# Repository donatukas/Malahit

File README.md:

* Malachite SDR

     * 50KHz-250MHz+400-2000MHz DSP SDR Receiver
     * DSP SDR Receiver for Malahit
     * Capacitive touch screen
     * Flash via USB cable
     * Default frequency range: 50KHz-2000MHz
     * 3.5 inch capacitive screen

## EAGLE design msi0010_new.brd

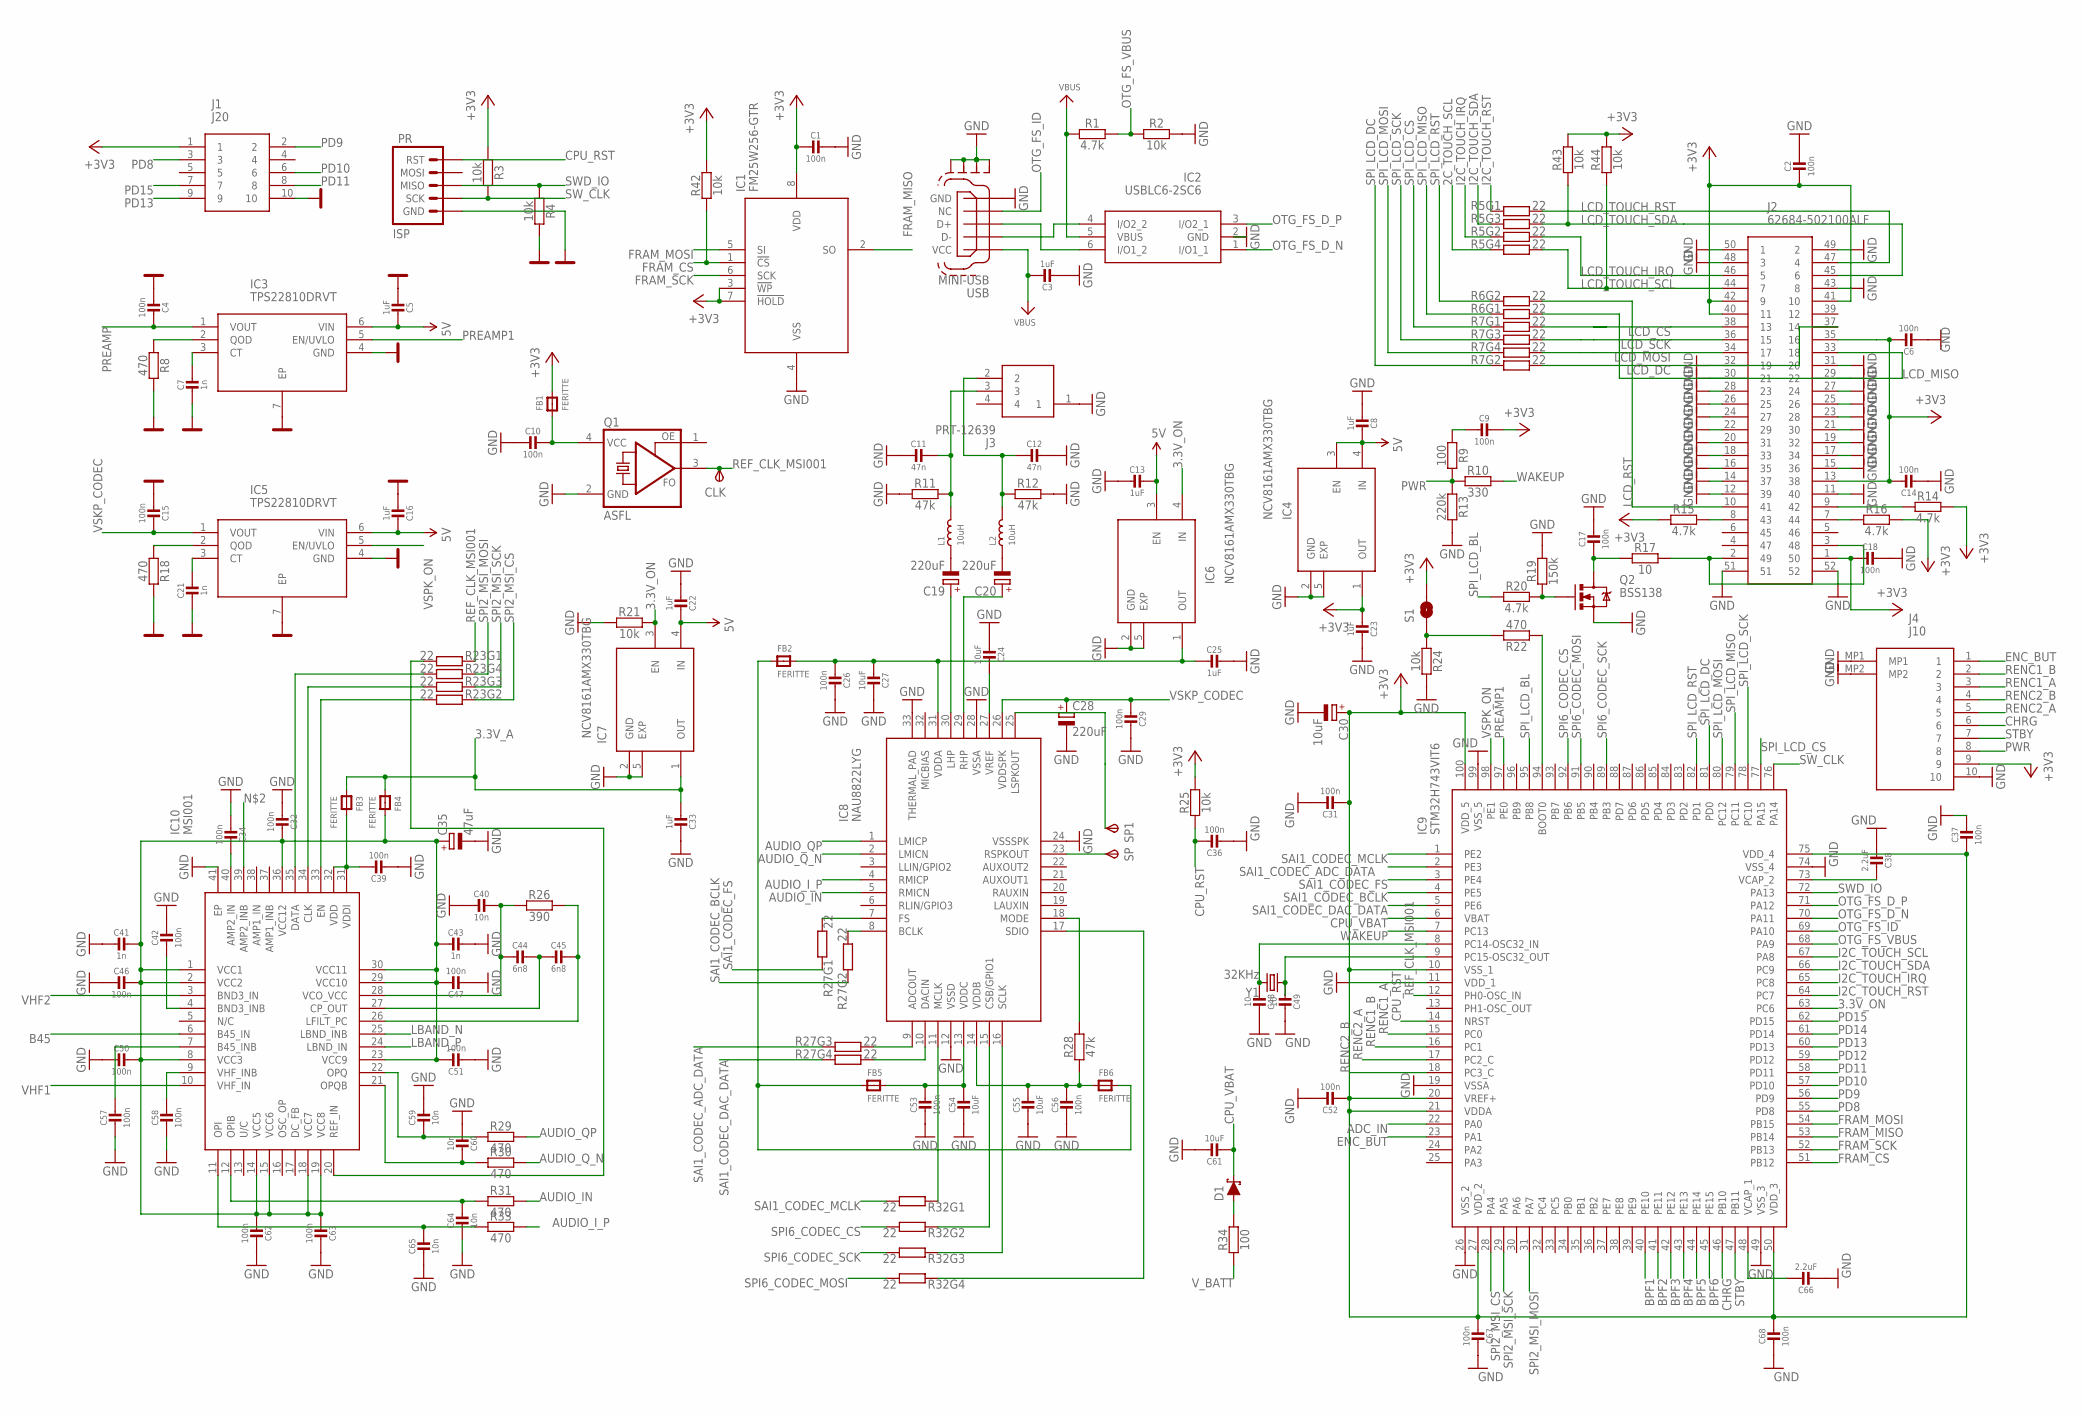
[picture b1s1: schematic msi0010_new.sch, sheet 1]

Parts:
C1, C2, C4, C6, C9, C10, C14, C15, C17, C18, C29, C31, C32, C34, C36, C37, C39, C42, C46, C47, C50, C51, C52, C53, C57, C58, C62, C63, C67, C68: 100n; _0402
C3, C5, C8, C13, C16, C22, C23, C25, C33: 1uF; _0603
C7, C21, C41, C43: 1n; _0402
C11, C12: 47n; _0402
C19, C20, C28: 220uF; SANYO-OSCON_A
C24, C27, C55, C61: 10uF; _0402
C26, C56: 100n; _0603
C30: 10uF; SMC_A
C35: 47uF; SMC_A
C38, C66: 2.2uF; 0805_NOTHERMALS
C40, C59, C60, C64, C65: 10n; _0402
C44, C45: 6n8; _0402
C48, C49: 10; _0402
C54: 10uF; _0603
CLK: TPSTP13R; TP13R
D1: 1A/40V/500mV; SOD-323
FB1, FB2, FB3, FB4, FB5, FB6: FERITTE; _0603
IC1: FM25W256-GTR; SOT127P602X173-8N
IC2: USBLC6-2SC6; SOT95P280X145-6N
IC3, IC5: TPS22810DRVT; SON65P200X200X80-7N
IC4, IC6, IC7: NCV8161AMX330TBG; VREG_NCP170AMX285TCG
IC8: NAU8822LYG; QFN50P500X500X80-33N
IC9: STM32H743VIT6; QFP50P1600X1600X160-100N
IC10: MSI001; QFN50P600X600X90-41N
J1: J20; 3220-10-0300-00-TR_322010030000TR
J2: 62684-502100ALF; 62684502100ALF
J3: PRT-12639; PRT12639
J4: J10; 686120148922_686120148922
L1, L2: 10uH; L0805@1
PR: ISP; SPARKFUN-CONNECTORS_PIC-ICSP-MINI
Q1: ASFL; ASF
Q2: BSS138; SOT23-3
R1, R14, R15, R16, R20: 4.7k; C0402
R2, R3, R4, R21, R24, R25, R42, R43, R44: 10k; C0402
R5, R6, R7, R23, R27, R32: 22; R_MATRIX_4_0402
R8, R18, R22, R29, R30, R31, R33: 470; C0402
R9, R34: 100; C0402
R10: 330; C0402
R11, R12, R28: 47k; C0402
R13: 220k; C0402
R17: 10; C0805
R19: 150k; C0402
R26: 390; C0402
S1: SOLDERJUMPERNO; SJ_2S-NO
SP, SP1: TPSTP15R; TP15R
USB: MINI-USB; MINI-USB-B5
Y1: 32KHz; CRYSTAL-32KHZ-MS3V

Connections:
2C_TOUCH_SCL: R5.4.1 (1)
3.3V_A: C33.2, FB3.1, FB4.1, IC7.1 (OUT); also elsewhere on the board
3.3V_ON: IC6.4 (IN), IC7.3 (EN), IC9.63 (PC6), R21.2
5V: C5.1, C8.1, C13.1, C16.1, C22.1, IC3.6 (VIN), IC4.3 (EN), IC4.4 (IN), IC5.6 (VIN), IC6.3 (EN), IC7.4 (IN); also elsewhere on the board
+3V3: C1.2, C2.2, C6.1, C9.1, C14.1, C18.2, C23.2, C30.+, C31.2, C37.2, C52.2, C67.2, C68.1, FB1.2, IC1.3 (!WP), IC1.7 (!HOLD), IC1.8 (VDD), IC4.1 (OUT), IC9.10 (VSS_1), IC9.20 (VREF+), IC9.21 (VDDA), IC9.27 (VDD_2), IC9.50 (VDD_3), IC9.75 (VDD_4), IC9.100 (VDD_5), J1.1, J2.1 (50), J2.13 (38), J2.35 (16), J2.40 (11), J2.41 (10), J2.42 (9), J4.9, R3.1, R14.2, R15.1, R16.2, R25.2, R42.2, R43.2, R44.2, S1.2; also elsewhere on the board
-: IC8.25 (LSPKOUT), SP1.TP
ADC_IN: IC9.22 (PA0); also elsewhere on the board
AUDIO_IN: IC8.5 (RMICN), R31.2
AUDIO_I_P: IC8.4 (RMICP), R33.2
AUDIO_QP: IC8.1 (LMICP), R29.2
AUDIO_Q_N: IC8.2 (LMICN), R30.2
B45: IC10.6 (B45_IN); also elsewhere on the board
BPF1: IC9.40 (PE10); also elsewhere on the board
BPF2: IC9.41 (PE11); also elsewhere on the board
BPF3: IC9.42 (PE12); also elsewhere on the board
BPF4: IC9.43 (PE13); also elsewhere on the board
BPF5: IC9.44 (PE14); also elsewhere on the board
BPF6: IC9.45 (PE15); also elsewhere on the board
CHRG: IC9.46 (PB10), J4.6; also elsewhere on the board
CPU_RST: C36.1, IC9.14 (NRST), PR.1 (RST), R25.1
CPU_VBAT: C61.2, D1.C, IC9.6 (VBAT)
ENC_BUT: IC9.23 (PA1), J4.1
FRAM_CS: IC1.1 (!CS), IC9.51 (PB12), R42.1
FRAM_MISO: IC1.2 (SO), IC9.53 (PB14)
FRAM_MOSI: IC1.5 (SI), IC9.54 (PB15)
FRAM_SCK: IC1.6 (SCK), IC9.52 (PB13)
GND: C1.1, C2.1, C3.2, C4.2, C5.2, C6.2, C7.2, C8.2, C10.2, C11.2, C12.1, C13.2, C14.2, C15.2, C16.2, C17.1, C18.1, C21.2, C22.2, C23.1, C24.2, C25.1, C26.1, C27.1, C28.-, C29.1, C30.-, C31.1, C32.2, C33.1, C34.2, C35.-, C36.2, C37.1, C38.2, C39.2, C40.2, C41.2, C42.1, C43.1, C46.2, C47.2, C48.1, C49.1, C50.2, C51.2, C52.1, C53.2, C54.2, C55.2, C56.2, C57.2, C58.2, C59.1, C60.2, C61.1, C62.1, C63.1, C64.2, C65.2, C66.2, C67.1, C68.2, IC1.4 (VSS), IC2.2 (GND), IC3.4 (GND), IC3.7 (EP), IC4.2 (GND), IC4.5 (EXP), IC5.4 (GND), IC5.7 (EP), IC6.2 (GND), IC6.5 (EXP), IC7.2 (GND), IC7.5 (EXP), IC8.12 (VSSD), IC8.24 (VSSSPK), IC8.28 (VSSA), IC8.33 (THERMAL_PAD), IC9.11 (VDD_1), IC9.19 (VSSA), IC9.26 (VSS_2), IC9.49 (VSS_3), IC9.74 (VSS_4), IC9.99 (VSS_5), IC10.41 (EP), J1.10, J2.11 (40), J2.12 (39), J2.14 (37), J2.15 (36), J2.16 (35), J2.17 (34), J2.18 (33), J2.19 (32), J2.20 (31), J2.21 (30), J2.22 (29), J2.23 (28), J2.24 (27), J2.25 (26), J2.26 (25), J2.27 (24), J2.28 (23), J2.29 (22), J2.30 (21), J2.31 (20), J2.32 (19), J2.43 (8), J2.48 (3), J2.49 (2), J2.50 (1), J2.51, J2.52, J3.1, J4.10, J4.MP1, J4.MP2, PR.5 (GND), Q1.2 (GND), Q2.2 (S), R2.2, R4.2, R8.2, R11.1, R12.2, R13.2, R18.2, R19.2, R21.1, R24.2, USB.5 (GND), USB.M1 (S1), USB.M2 (S2), USB.M3 (S3), USB.M4 (S4); also elsewhere on the board
I2C_TOUCH_IRQ: IC9.65 (PC8), R5.2.1 (1)
I2C_TOUCH_RST: IC9.64 (PC7), R5.1.1 (1)
I2C_TOUCH_SCL: IC9.67 (PA8)
I2C_TOUCH_SDA: IC9.66 (PC9), R5.3.1 (1)
IO15: C48.2, IC9.8 (PC14-OSC32_IN), Y1.P$2 (2)
IO16: C49.2, IC9.9 (PC15-OSC32_OUT), Y1.P$1 (1)
LBAND_N: IC10.25 (LBND_INB); also elsewhere on the board
LBAND_P: IC10.24 (LBND_IN); also elsewhere on the board
LCD_CS: J2.38 (13), R7.1.2 (2)
LCD_DC: J2.37 (14), R7.2.2 (2)
LCD_MISO: J2.33 (18), R6.1.2 (2)
LCD_MOSI: J2.34 (17), R7.4.2 (2)
LCD_RST: J2.10 (41), R6.2.2 (2)
LCD_SCK: J2.36 (15), R7.3.2 (2)
LCD_TOUCH_IRQ: J2.46 (5), R5.2.2 (2)
LCD_TOUCH_RST: J2.47 (4), R5.1.2 (2)
LCD_TOUCH_SCL: J2.44 (7), R5.4.2 (2), R44.1
LCD_TOUCH_SDA: J2.45 (6), R5.3.2 (2), R43.1
unnamed: C34.1, IC10.40 (AMP2_IN)
unnamed 48: IC10.39 (AMP2_INB); also elsewhere on the board
unnamed: C39.1, FB3.2, IC10.31 (VDDI), IC10.32 (VDD)
unnamed: C32.1, C35.+, C41.1, C43.2, C46.1, C47.1, C50.1, C51.1, C62.2, C63.2, FB4.2, IC10.1 (VCC1), IC10.2 (VCC2), IC10.8 (VCC3), IC10.14 (VCC5), IC10.15 (VCC6), IC10.18 (VCC7), IC10.19 (VCC8), IC10.23 (VCC9), IC10.29 (VCC10), IC10.30 (VCC11), IC10.36 (VCC12)
unnamed: C64.1, IC10.12 (OPIB), R31.1
unnamed: C65.1, IC10.11 (OPI), R33.1
unnamed: C60.1, IC10.21 (OPQB), R30.1
unnamed: C59.2, IC10.22 (OPQ), R29.1
unnamed: C21.1, IC5.3 (CT)
unnamed: C10.1, FB1.1, Q1.4 (VCC)
unnamed: C42.2, IC10.4 (BND3_INB)
unnamed: C58.1, IC10.9 (VHF_INB)
unnamed: C57.1, IC10.7 (B45_INB)
unnamed: IC10.33 (EN), R23.2.2 (2)
unnamed: IC10.34 (CLK), R23.3.2 (2)
unnamed: IC10.35 (DATA), R23.4.2 (2)
unnamed: C40.1, C44.2, IC10.28 (VCO_VCC), R26.1
unnamed: C44.1, C45.2, IC10.27 (CP_OUT)
unnamed: C45.1, IC10.26 (LFILT_PC), R26.2
unnamed: C19.+, IC8.30 (LHP)
unnamed: IC10.20 (REF_IN), R23.1.2 (2)
unnamed: C24.1, IC8.27 (VREF)
unnamed: C25.2, C26.2, C27.2, FB2.2, IC6.1 (OUT), IC8.31 (VDDA)
unnamed: C53.1, C54.1, FB5.2, IC8.13 (VDDC)
unnamed: FB2.1, FB5.1, FB6.2
unnamed: C55.1, C56.1, FB6.1, IC8.14 (VDDB), R28.1
unnamed: IC8.18 (MODE), R28.2
unnamed: C20.+, IC8.29 (RHP)
unnamed: IC8.7 (FS), R27.1.2 (2)
unnamed: IC8.8 (BCLK), R27.2.2 (2)
unnamed: IC8.9 (ADCOUT), R27.3.2 (2)
unnamed: IC8.10 (DACIN), R27.4.2 (2)
unnamed: C7.1, IC3.3 (CT)
unnamed: IC5.2 (QOD), R18.1
unnamed: IC8.15 (CSB/GPIO1), R32.2.1 (1)
unnamed: IC8.11 (MCLK), R32.1.1 (1)
unnamed: IC8.16 (SCLK), R32.3.1 (1)
unnamed: IC8.17 (SDIO), R32.4.1 (1)
unnamed: C19.-, L1.1
unnamed: C20.-, L2.1
unnamed: C12.2, J3.2, L2.2, R12.1
unnamed: IC3.2 (QOD), R8.1
unnamed: C11.1, J3.3, L1.2, R11.2
unnamed: IC2.6 (I/O1_2), USB.3 (D+)
unnamed: J2.2 (49), J2.3 (48), R17.2
unnamed: J2.7 (44), R16.1
unnamed: C17.2, Q2.3 (D), R17.1
unnamed: Q2.1 (G), R19.1, R20.2
unnamed: J2.9 (42), R14.1
unnamed: J2.8 (43), R15.2
unnamed: C66.1, IC9.48 (VCAP_1)
unnamed: C38.1, IC9.73 (VCAP_2)
unnamed: IC8.23 (RSPKOUT), SP.TP
unnamed: IC2.4 (I/O2_2), USB.2 (D-)
unnamed: R22.2, R24.1, S1.1
unnamed: IC9.94 (BOOT0), R22.1
unnamed: C9.2, R9.1
OTG_FS_D_N: IC2.1 (I/O1_1), IC9.70 (PA11)
OTG_FS_D_P: IC2.3 (I/O2_1), IC9.71 (PA12)
OTG_FS_ID: IC9.69 (PA10), USB.4 (NC)
OTG_FS_VBUS: IC9.68 (PA9), R1.2, R2.1
PD8: IC9.55 (PD8), J1.3
PD9: IC9.56 (PD9), J1.2
PD10: IC9.57 (PD10), J1.6
PD11: IC9.58 (PD11), J1.8
PD12: IC9.59 (PD12)
PD13: IC9.60 (PD13), J1.9
PD14: IC9.61 (PD14)
PD15: IC9.62 (PD15), J1.7
PREAMP: C4.1, IC3.1 (VOUT); also elsewhere on the board
PREAMP1: IC3.5 (EN/UVLO), IC9.97 (PE0); also elsewhere on the board
PWR: J4.8, R9.2, R10.1, R13.1
REF_CLK_MSI001: CLK.TP, IC9.12 (PH0-OSC_IN), Q1.3 (FO), R23.1.1 (1)
RENC1_A: IC9.15 (PC0), J4.3
RENC1_B: IC9.16 (PC1), J4.2
RENC2_A: IC9.17 (PC2_C), J4.5
RENC2_B: IC9.18 (PC3_C), J4.4
SAI1_CODEC_ADC_DATA: IC9.2 (PE3), R27.3.1 (1)
SAI1_CODEC_BCLK: IC9.4 (PE5), R27.2.1 (1)
SAI1_CODEC_DAC_DATA: IC9.5 (PE6), R27.4.1 (1)
SAI1_CODEC_FS: IC9.3 (PE4), R27.1.1 (1)
SAI1_CODEC_MCLK: IC9.1 (PE2), R32.1.2 (2)
SPI2_MSI_CS: IC9.28 (PA4), R23.2.1 (1)
SPI2_MSI_MOSI: IC9.31 (PA7), R23.4.1 (1)
SPI2_MSI_SCK: IC9.29 (PA5), R23.3.1 (1)
SPI6_CODEC_CS: IC9.92 (PB6), R32.2.2 (2)
SPI6_CODEC_MOSI: IC9.91 (PB5), R32.4.2 (2)
SPI6_CODEC_SCK: IC9.89 (PB3), R32.3.2 (2)
SPI_LCD_BL: IC9.95 (PB8), R20.1
SPI_LCD_CS: IC9.77 (PA15), R7.1.1 (1)
SPI_LCD_DC: IC9.81 (PD0), R7.2.1 (1)
SPI_LCD_MISO: IC9.79 (PC11), R6.1.1 (1)
SPI_LCD_MOSI: IC9.80 (PC12), R7.4.1 (1)
SPI_LCD_RST: IC9.82 (PD1), R6.2.1 (1)
SPI_LCD_SCK: IC9.78 (PC10), R7.3.1 (1)
STBY: IC9.47 (PB11), J4.7; also elsewhere on the board
SWD_IO: IC9.72 (PA13), PR.3 (MISO), R4.1
SW_CLK: IC9.76 (PA14), PR.4 (SCK), R3.2
VBUS: C3.1, IC2.5 (VBUS), R1.1, USB.1 (VCC); also elsewhere on the board
VBUS1: D1.A, R34.2
VHF1: IC10.10 (VHF_IN); also elsewhere on the board
VHF2: IC10.3 (BND3_IN); also elsewhere on the board
VSKP_CODEC: C15.1, C28.+, C29.2, IC5.1 (VOUT), IC8.26 (VDDSPK)
VSPK_ON: IC5.5 (EN/UVLO), IC9.98 (PE1)
V_BATT: R34.1; also elsewhere on the board
WAKEUP: IC9.7 (PC13), R10.2

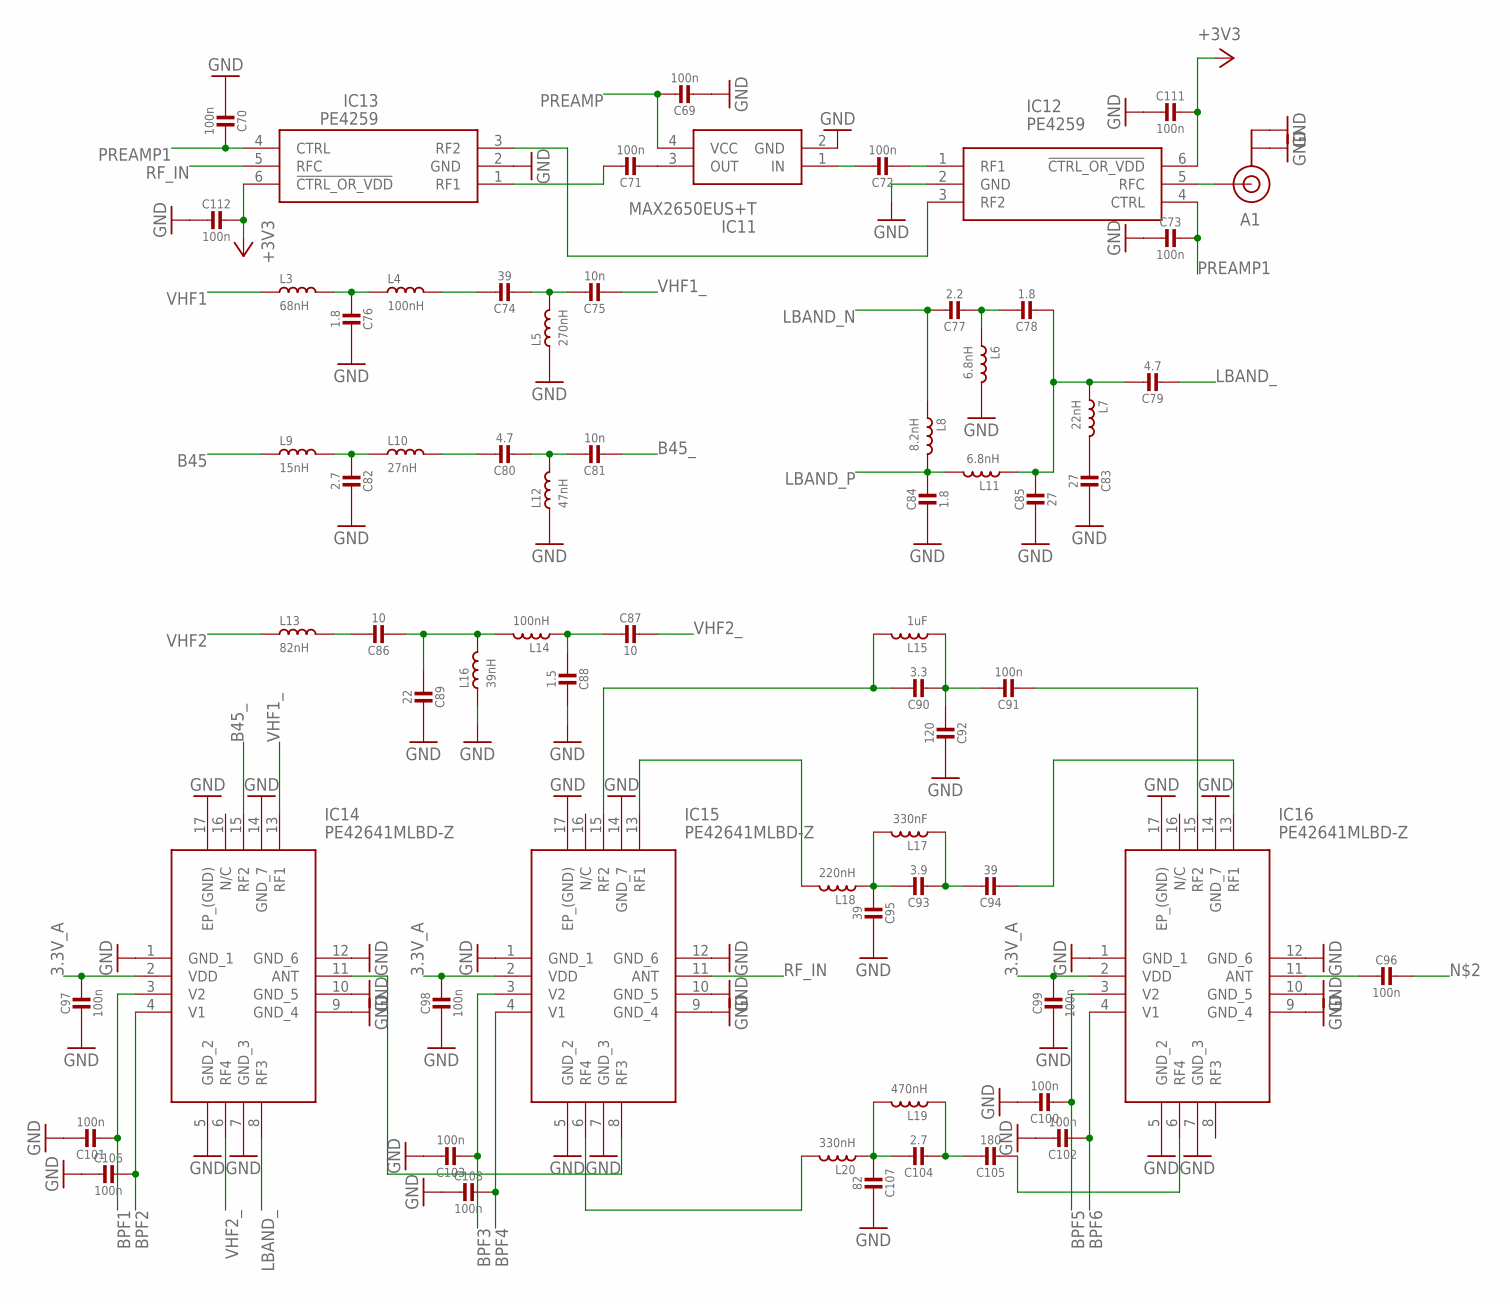
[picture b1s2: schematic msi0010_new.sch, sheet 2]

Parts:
A1: U.FL
C69, C70, C71, C72, C73, C91, C96, C97, C98, C99, C100, C101, C102, C103, C106, C108, C111, C112: 100n; _0402
C74, C94, C95: 39; _0402
C75, C81: 10n; _0402
C76, C78, C84: 1.8; _0402
C77: 2.2; _0402
C79, C80: 4.7; _0402
C82, C104: 2.7; _0402
C83, C85: 27; _0402
C86, C87: 10; _0402
C88: 1.5; _0402
C89: 22; _0402
C90: 3.3; _0402
C92: 120; _0402
C93: 3.9; _0402
C105: 180; _0402
C107: 82; _0402
IC11: MAX2650EUS+T; 4-SOT143
IC12: PE4259; SOT65P210X110-6N
IC13: PE4259; SOT65P210X110-6N; MANUFACTURER_PART_NUMBER PE4259; MOUSER_PART_NUMBER N/A
IC14: PE42641MLBD-Z; QFN50P300X300X80-17N
IC15, IC16: PE42641MLBD-Z; QFN50P300X300X80-17N; MANUFACTURER_PART_NUMBER PE42641MLBD-Z; MOUSER_PART_NUMBER 81-PE42641MLBD-Z
L3: 68nH; L0603@1
L4: 100nH; L0603@1
L5: 270nH; L0603@1
L6, L11: 6.8nH; L0402@1
L7: 22nH; L0402@1
L8: 8.2nH; L0402@1
L9: 15nH; L0402@1
L10: 27nH; L0402@1
L12: 47nH; L0402@1
L13: 82nH; L0603@1
L14: 100nH; L0402@1
L15: 1uF; L0805@1
L16: 39nH; L0402@1
L17: 330nF; L0603@1
L18: 220nH; L0603@1
L19: 470nH; L0603@1
L20: 330nH; L0603@1

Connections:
3.3V_A: C97.1, C98.1, C99.1, IC14.2 (VDD), IC15.2 (VDD), IC16.2 (VDD); also elsewhere on the board
+3V3: C111.1, C112.1, IC12.6 (!CTRL_OR_VDD), IC13.6 (!CTRL_OR_VDD); also elsewhere on the board
B45: L9.1; also elsewhere on the board
B45_: C81.2, IC14.15 (RF2)
BPF1: C101.2, IC14.3 (V2); also elsewhere on the board
BPF2: C106.1, IC14.4 (V1); also elsewhere on the board
BPF3: C103.2, IC15.3 (V2); also elsewhere on the board
BPF4: C108.1, IC15.4 (V1); also elsewhere on the board
BPF5: C100.2, IC16.3 (V2); also elsewhere on the board
BPF6: C102.2, IC16.4 (V1); also elsewhere on the board
GND: A1.P$1 (GND), A1.P$2 (GND), C69.2, C70.2, C73.2, C76.1, C82.1, C83.1, C84.2, C85.2, C88.1, C89.1, C92.1, C95.1, C97.2, C98.2, C99.2, C100.1, C101.1, C102.1, C103.1, C106.2, C107.1, C108.2, C111.2, C112.2, IC11.2 (GND), IC12.2 (GND), IC13.2 (GND), IC14.1 (GND_1), IC14.5 (GND_2), IC14.7 (GND_3), IC14.9 (GND_4), IC14.10 (GND_5), IC14.12 (GND_6), IC14.14 (GND_7), IC14.17 (EP_(GND)), IC15.1 (GND_1), IC15.5 (GND_2), IC15.7 (GND_3), IC15.9 (GND_4), IC15.10 (GND_5), IC15.12 (GND_6), IC15.14 (GND_7), IC15.17 (EP_(GND)), IC16.1 (GND_1), IC16.5 (GND_2), IC16.7 (GND_3), IC16.9 (GND_4), IC16.10 (GND_5), IC16.12 (GND_6), IC16.14 (GND_7), IC16.17 (EP_(GND)), L5.1, L6.2, L12.1, L16.1; also elsewhere on the board
LBAND_: C79.2, IC14.8 (RF3)
LBAND_N: C77.1, L8.1; also elsewhere on the board
LBAND_P: C84.1, L8.2, L11.2; also elsewhere on the board
unnamed 48: C96.1; also elsewhere on the board
unnamed: C71.1, IC13.1 (RF1)
unnamed: C82.2, L9.2, L10.1
unnamed: C78.2, C79.1, C85.1, L7.1, L11.1
unnamed: C80.1, L10.2
unnamed: C77.2, C78.1, L6.1
unnamed: C83.2, L7.2
unnamed: C80.2, C81.1, L12.2
unnamed: C76.2, L3.2, L4.1
unnamed: C74.1, L4.2
unnamed: C74.2, C75.1, L5.2
unnamed: IC14.11 (ANT), IC15.8 (RF3)
unnamed: C86.1, L13.2
unnamed: C86.2, C89.2, L14.2, L16.2
unnamed: C87.2, C88.2, L14.1
unnamed: C90.1, IC15.15 (RF2), L15.2
unnamed: C90.2, C91.1, C92.2, L15.1
unnamed: C72.1, IC11.1 (IN)
unnamed: C91.2, IC16.15 (RF2)
unnamed: C104.1, C107.2, L19.2, L20.1
unnamed: C104.2, C105.1, L19.1
unnamed: IC15.6 (RF4), L20.2
unnamed: C105.2, IC16.6 (RF4)
unnamed: C93.1, C95.2, L17.2, L18.1
unnamed: C93.2, C94.1, L17.1
unnamed: IC15.13 (RF1), L18.2
unnamed: C94.2, IC16.13 (RF1)
unnamed: C71.2, IC11.3 (OUT)
unnamed: C72.2, IC12.1 (RF1)
unnamed: A1.P$3 (SIGNAL), IC12.5 (RFC)
unnamed: C96.2, IC16.11 (ANT)
unnamed: IC12.3 (RF2), IC13.3 (RF2)
PREAMP: C69.1, IC11.4 (VCC); also elsewhere on the board
PREAMP1: C70.1, C73.1, IC12.4 (CTRL), IC13.4 (CTRL); also elsewhere on the board
RF_IN: IC13.5 (RFC), IC15.11 (ANT)
VHF1: L3.1; also elsewhere on the board
VHF1_: C75.2, IC14.13 (RF1)
VHF2: L13.1; also elsewhere on the board
VHF2_: C87.1, IC14.6 (RF4)

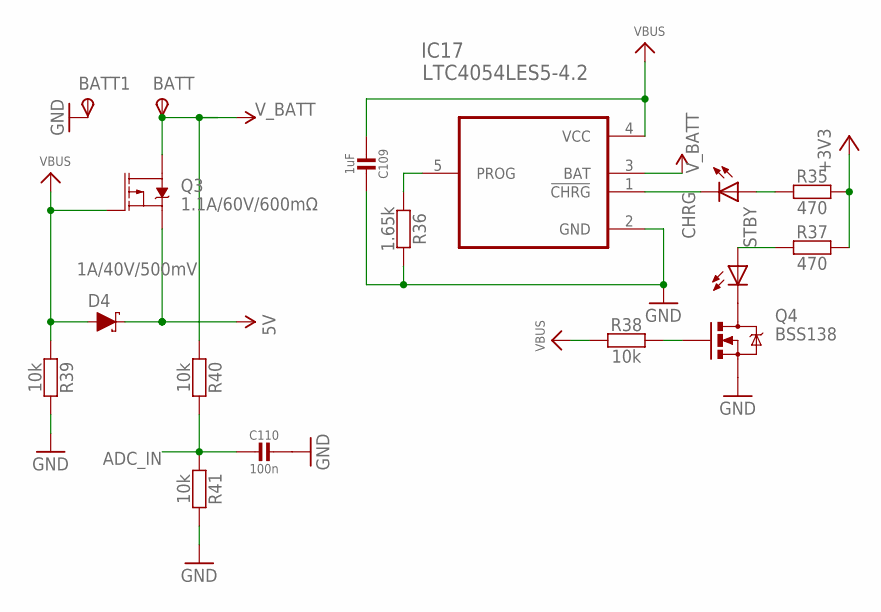
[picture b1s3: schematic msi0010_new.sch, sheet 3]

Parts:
BATT, BATT1: TPSTP13R; TP13R
C109: 1uF; _0603
C110: 100n; _0402
D2, D3: 1 led; LED-0603
D4: 1A/40V/500mV; SOD-323
IC17: LTC4054LES5-4.2; SOT95P280X100-5N
Q3: 1.1A/60V/600mΩ; SOT23-3@1
Q4: BSS138; SOT23-3
R35, R37: 470; C0402
R36: 1.65k; C0402
R38, R39, R40, R41: 10k; C0402

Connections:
5V: D4.C, Q3.2 (S); also elsewhere on the board
+3V3: R35.2, R37.2; also elsewhere on the board
ADC_IN: C110.2, R40.2, R41.1; also elsewhere on the board
CHRG: D2.C, IC17.1 (!CHRG); also elsewhere on the board
GND: BATT1.TP, C109.1, C110.1, IC17.2 (GND), Q4.2 (S), R36.2, R39.2, R41.2; also elsewhere on the board
unnamed: IC17.5 (PROG), R36.1
unnamed: D2.A, R35.1
unnamed: D3.C, Q4.3 (D)
unnamed: Q4.1 (G), R38.2
STBY: D3.A, R37.1; also elsewhere on the board
VBUS: C109.2, D4.A, IC17.4 (VCC), Q3.1 (G), R38.1, R39.1; also elsewhere on the board
V_BATT: BATT.TP, IC17.3 (BAT), Q3.3 (D), R40.1; also elsewhere on the board

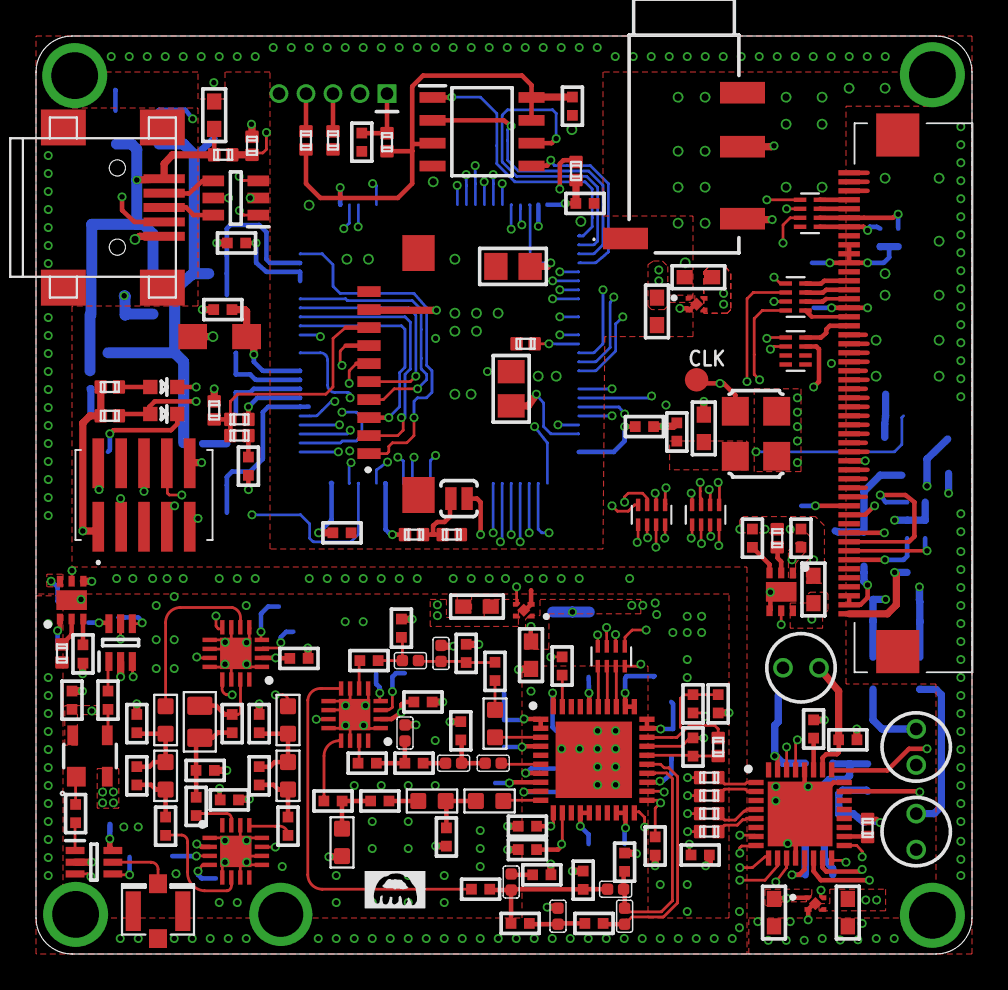
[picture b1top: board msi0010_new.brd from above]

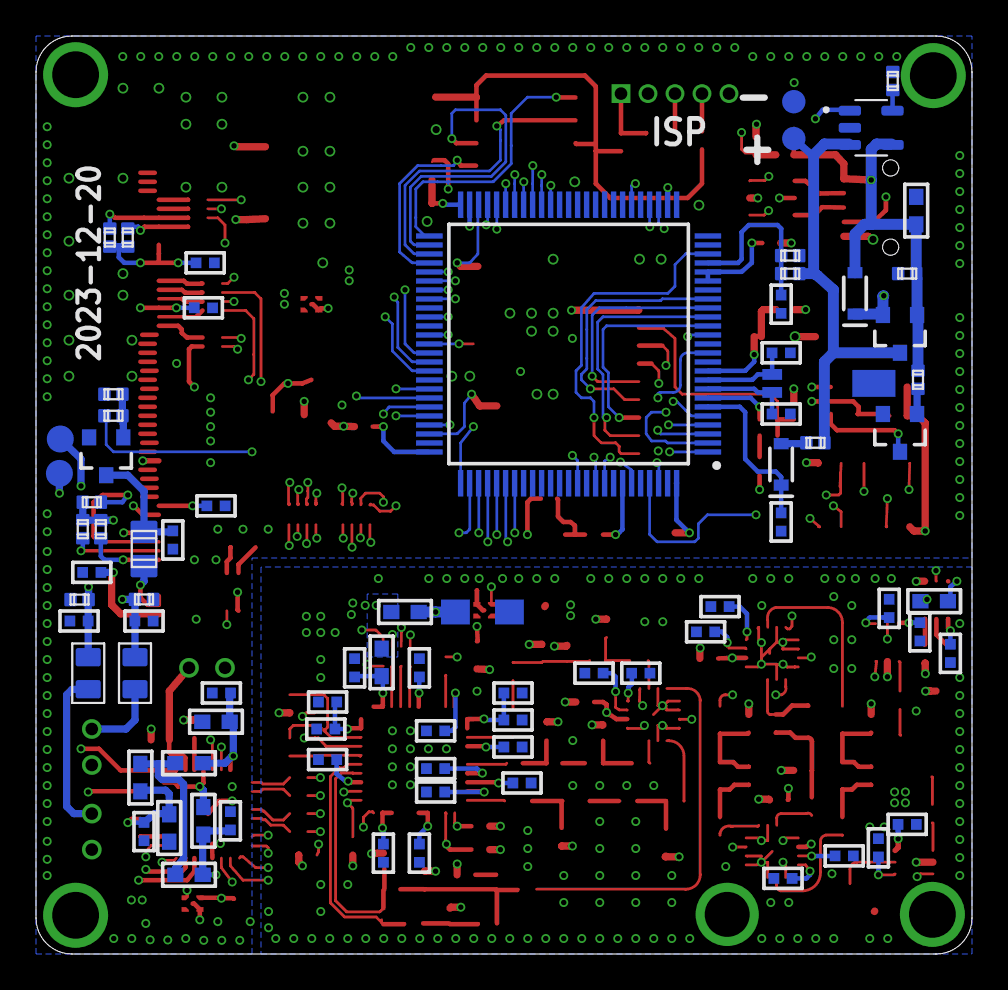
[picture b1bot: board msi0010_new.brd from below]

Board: 6 copper layers, 52.0 x 51.0 mm, 221 parts (80 on the bottom side), 187 nets.

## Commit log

2024-02-07 malahit
    malahit

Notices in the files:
parts and their libraries:
microbuilder: This work is placed in the public domain, and may be freely used for commercial and non-commercial work with the following conditions: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
SparkFun-DiscreteSemi: Licensing: Creative Commons ShareAlike 4.0 International - https://creativecommons.org/licenses/by-sa/4.0
